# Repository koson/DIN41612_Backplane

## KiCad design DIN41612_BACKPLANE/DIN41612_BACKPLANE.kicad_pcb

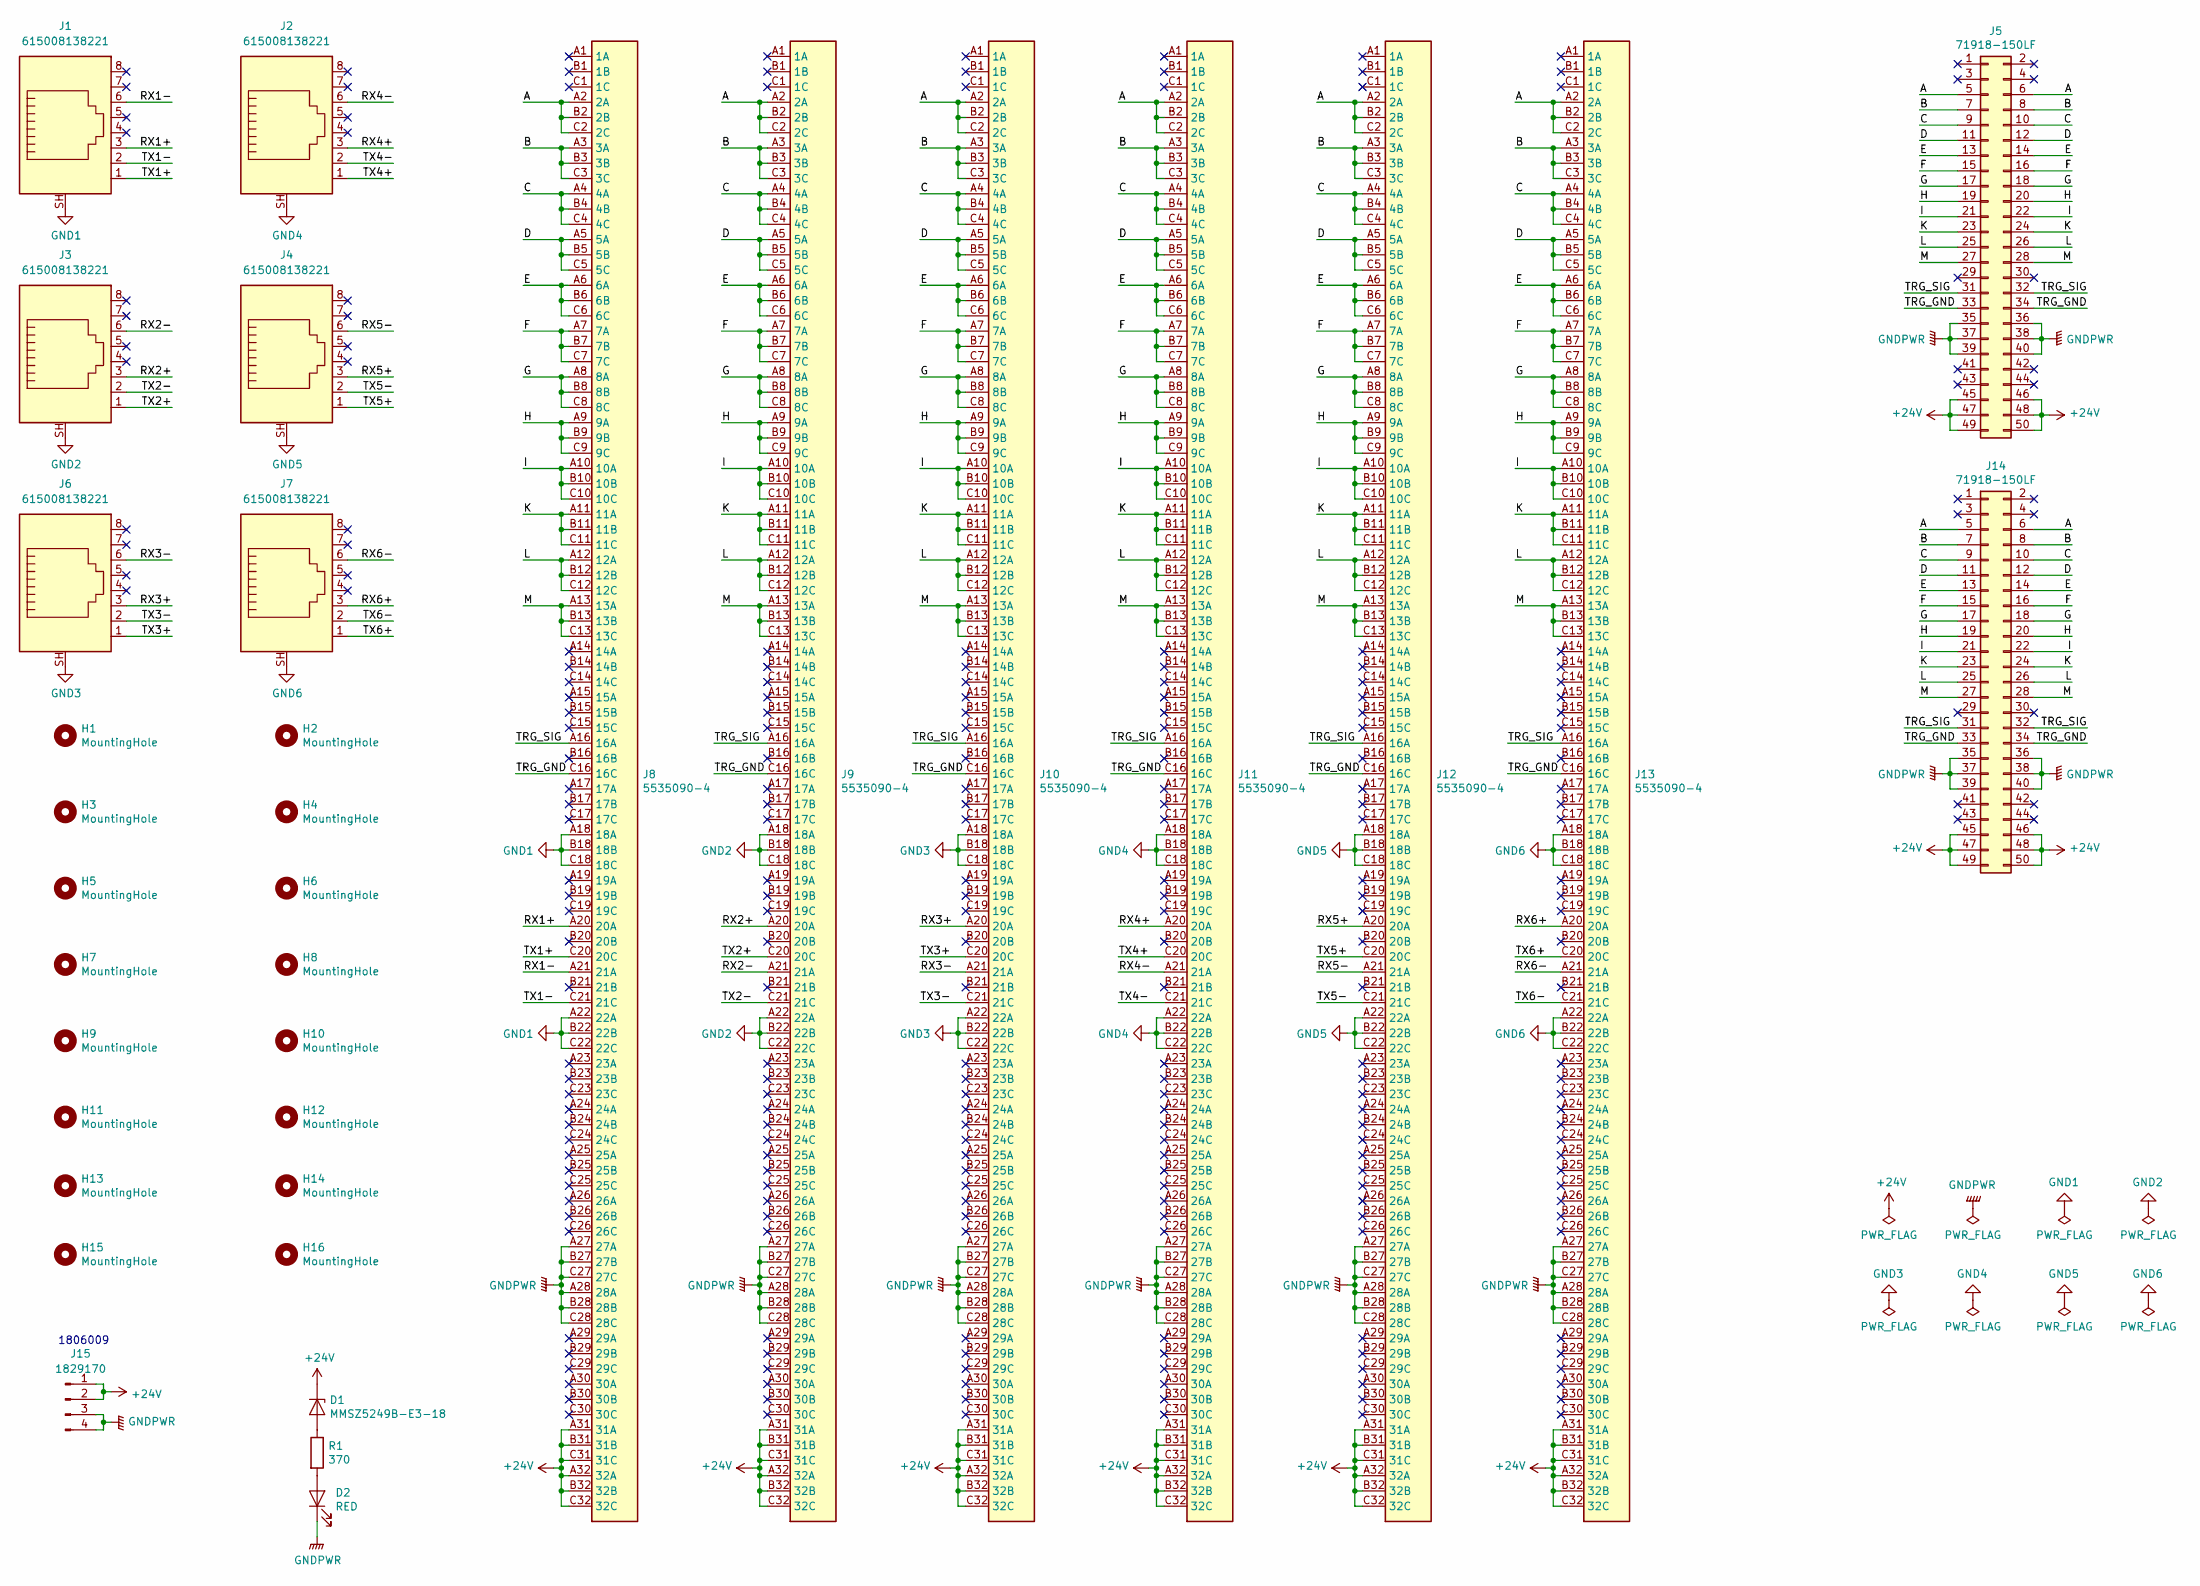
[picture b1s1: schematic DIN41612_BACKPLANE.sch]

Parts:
D1: MMSZ5249B-E3-18; D_SOD-123
D2: RED; LED_0603_1608Metric_Pad1.05x0.95mm_HandSolder
H1, H2, H3, H4, H5, H6, H7, H8, H9, H10, H11, H12, H13, H14, H15, H16: MountingHole; MountingHole_3.2mm_M3_DIN965_Pad
J1, J2, J3, J4, J6, J7: 615008138221
J5, J14: 71918-150LF; IDC-Header_2x25_P2.54mm_Vertical_Lock
J8, J9, J10, J11, J12, J13: 5535090-4; C96ABC
J15: 1829170; PhoenixContact_GMSTBV_2,5_4-GF-7,62_1x04_P7.62mm_Vertical_T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
R1: 370; R_0603_1608Metric_Pad1.05x0.95mm_HandSolder

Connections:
+24V: D1.1 (K), J5.45, J5.46, J5.47, J5.48, J5.49, J5.50, J8.A31 (31A), J8.A32 (32A), J8.B31 (31B), J8.B32 (32B), J8.C31 (31C), J8.C32 (32C), J9.A31 (31A), J9.A32 (32A), J9.B31 (31B), J9.B32 (32B), J9.C31 (31C), J9.C32 (32C), J10.A31 (31A), J10.A32 (32A), J10.B31 (31B), J10.B32 (32B), J10.C31 (31C), J10.C32 (32C), J11.A31 (31A), J11.A32 (32A), J11.B31 (31B), J11.B32 (32B), J11.C31 (31C), J11.C32 (32C), J12.A31 (31A), J12.A32 (32A), J12.B31 (31B), J12.B32 (32B), J12.C31 (31C), J12.C32 (32C), J13.A31 (31A), J13.A32 (32A), J13.B31 (31B), J13.B32 (32B), J13.C31 (31C), J13.C32 (32C), J14.45, J14.46, J14.47, J14.48, J14.49, J14.50, J15.1, J15.2
/A: J5.5, J5.6, J8.A2 (2A), J8.B2 (2B), J8.C2 (2C), J9.A2 (2A), J9.B2 (2B), J9.C2 (2C), J10.A2 (2A), J10.B2 (2B), J10.C2 (2C), J11.A2 (2A), J11.B2 (2B), J11.C2 (2C), J12.A2 (2A), J12.B2 (2B), J12.C2 (2C), J13.A2 (2A), J13.B2 (2B), J13.C2 (2C), J14.5, J14.6
/B: J5.7, J5.8, J8.A3 (3A), J8.B3 (3B), J8.C3 (3C), J9.A3 (3A), J9.B3 (3B), J9.C3 (3C), J10.A3 (3A), J10.B3 (3B), J10.C3 (3C), J11.A3 (3A), J11.B3 (3B), J11.C3 (3C), J12.A3 (3A), J12.B3 (3B), J12.C3 (3C), J13.A3 (3A), J13.B3 (3B), J13.C3 (3C), J14.7, J14.8
/C: J5.9, J5.10, J8.A4 (4A), J8.B4 (4B), J8.C4 (4C), J9.A4 (4A), J9.B4 (4B), J9.C4 (4C), J10.A4 (4A), J10.B4 (4B), J10.C4 (4C), J11.A4 (4A), J11.B4 (4B), J11.C4 (4C), J12.A4 (4A), J12.B4 (4B), J12.C4 (4C), J13.A4 (4A), J13.B4 (4B), J13.C4 (4C), J14.9, J14.10
/D: J5.11, J5.12, J8.A5 (5A), J8.B5 (5B), J8.C5 (5C), J9.A5 (5A), J9.B5 (5B), J9.C5 (5C), J10.A5 (5A), J10.B5 (5B), J10.C5 (5C), J11.A5 (5A), J11.B5 (5B), J11.C5 (5C), J12.A5 (5A), J12.B5 (5B), J12.C5 (5C), J13.A5 (5A), J13.B5 (5B), J13.C5 (5C), J14.11, J14.12
/E: J5.13, J5.14, J8.A6 (6A), J8.B6 (6B), J8.C6 (6C), J9.A6 (6A), J9.B6 (6B), J9.C6 (6C), J10.A6 (6A), J10.B6 (6B), J10.C6 (6C), J11.A6 (6A), J11.B6 (6B), J11.C6 (6C), J12.A6 (6A), J12.B6 (6B), J12.C6 (6C), J13.A6 (6A), J13.B6 (6B), J13.C6 (6C), J14.13, J14.14
/F: J5.15, J5.16, J8.A7 (7A), J8.B7 (7B), J8.C7 (7C), J9.A7 (7A), J9.B7 (7B), J9.C7 (7C), J10.A7 (7A), J10.B7 (7B), J10.C7 (7C), J11.A7 (7A), J11.B7 (7B), J11.C7 (7C), J12.A7 (7A), J12.B7 (7B), J12.C7 (7C), J13.A7 (7A), J13.B7 (7B), J13.C7 (7C), J14.15, J14.16
/G: J5.17, J5.18, J8.A8 (8A), J8.B8 (8B), J8.C8 (8C), J9.A8 (8A), J9.B8 (8B), J9.C8 (8C), J10.A8 (8A), J10.B8 (8B), J10.C8 (8C), J11.A8 (8A), J11.B8 (8B), J11.C8 (8C), J12.A8 (8A), J12.B8 (8B), J12.C8 (8C), J13.A8 (8A), J13.B8 (8B), J13.C8 (8C), J14.17, J14.18
/H: J5.19, J5.20, J8.A9 (9A), J8.B9 (9B), J8.C9 (9C), J9.A9 (9A), J9.B9 (9B), J9.C9 (9C), J10.A9 (9A), J10.B9 (9B), J10.C9 (9C), J11.A9 (9A), J11.B9 (9B), J11.C9 (9C), J12.A9 (9A), J12.B9 (9B), J12.C9 (9C), J13.A9 (9A), J13.B9 (9B), J13.C9 (9C), J14.19, J14.20
/I: J5.21, J5.22, J8.A10 (10A), J8.B10 (10B), J8.C10 (10C), J9.A10 (10A), J9.B10 (10B), J9.C10 (10C), J10.A10 (10A), J10.B10 (10B), J10.C10 (10C), J11.A10 (10A), J11.B10 (10B), J11.C10 (10C), J12.A10 (10A), J12.B10 (10B), J12.C10 (10C), J13.A10 (10A), J13.B10 (10B), J13.C10 (10C), J14.21, J14.22
/K: J5.23, J5.24, J8.A11 (11A), J8.B11 (11B), J8.C11 (11C), J9.A11 (11A), J9.B11 (11B), J9.C11 (11C), J10.A11 (11A), J10.B11 (11B), J10.C11 (11C), J11.A11 (11A), J11.B11 (11B), J11.C11 (11C), J12.A11 (11A), J12.B11 (11B), J12.C11 (11C), J13.A11 (11A), J13.B11 (11B), J13.C11 (11C), J14.23, J14.24
/L: J5.25, J5.26, J8.A12 (12A), J8.B12 (12B), J8.C12 (12C), J9.A12 (12A), J9.B12 (12B), J9.C12 (12C), J10.A12 (12A), J10.B12 (12B), J10.C12 (12C), J11.A12 (12A), J11.B12 (12B), J11.C12 (12C), J12.A12 (12A), J12.B12 (12B), J12.C12 (12C), J13.A12 (12A), J13.B12 (12B), J13.C12 (12C), J14.25, J14.26
/M: J5.27, J5.28, J8.A13 (13A), J8.B13 (13B), J8.C13 (13C), J9.A13 (13A), J9.B13 (13B), J9.C13 (13C), J10.A13 (13A), J10.B13 (13B), J10.C13 (13C), J11.A13 (13A), J11.B13 (13B), J11.C13 (13C), J12.A13 (13A), J12.B13 (13B), J12.C13 (13C), J13.A13 (13A), J13.B13 (13B), J13.C13 (13C), J14.27, J14.28
/RX1+: J1.3, J8.A20 (20A)
/RX1-: J1.6, J8.A21 (21A)
/RX2+: J3.3, J9.A20 (20A)
/RX2-: J3.6, J9.A21 (21A)
/RX3+: J6.3, J10.A20 (20A)
/RX3-: J6.6, J10.A21 (21A)
/RX4+: J2.3, J11.A20 (20A)
/RX4-: J2.6, J11.A21 (21A)
/RX5+: J4.3, J12.A20 (20A)
/RX5-: J4.6, J12.A21 (21A)
/RX6+: J7.3, J13.A20 (20A)
/RX6-: J7.6, J13.A21 (21A)
/TRG_GND: J5.33, J5.34, J8.C16 (16C), J9.C16 (16C), J10.C16 (16C), J11.C16 (16C), J12.C16 (16C), J13.C16 (16C), J14.33, J14.34
/TRG_SIG: J5.31, J5.32, J8.A16 (16A), J9.A16 (16A), J10.A16 (16A), J11.A16 (16A), J12.A16 (16A), J13.A16 (16A), J14.31, J14.32
/TX1+: J1.1, J8.C20 (20C)
/TX1-: J1.2, J8.C21 (21C)
/TX2+: J3.1, J9.C20 (20C)
/TX2-: J3.2, J9.C21 (21C)
/TX3+: J6.1, J10.C20 (20C)
/TX3-: J6.2, J10.C21 (21C)
/TX4+: J2.1, J11.C20 (20C)
/TX4-: J2.2, J11.C21 (21C)
/TX5+: J4.1, J12.C20 (20C)
/TX5-: J4.2, J12.C21 (21C)
/TX6+: J7.1, J13.C20 (20C)
/TX6-: J7.2, J13.C21 (21C)
GND1: J1.SH, J8.A18 (18A), J8.A22 (22A), J8.B18 (18B), J8.B22 (22B), J8.C18 (18C), J8.C22 (22C)
GND2: J3.SH, J9.A18 (18A), J9.A22 (22A), J9.B18 (18B), J9.B22 (22B), J9.C18 (18C), J9.C22 (22C)
GND3: J6.SH, J10.A18 (18A), J10.A22 (22A), J10.B18 (18B), J10.B22 (22B), J10.C18 (18C), J10.C22 (22C)
GND4: J2.SH, J11.A18 (18A), J11.A22 (22A), J11.B18 (18B), J11.B22 (22B), J11.C18 (18C), J11.C22 (22C)
GND5: J4.SH, J12.A18 (18A), J12.A22 (22A), J12.B18 (18B), J12.B22 (22B), J12.C18 (18C), J12.C22 (22C)
GND6: J7.SH, J13.A18 (18A), J13.A22 (22A), J13.B18 (18B), J13.B22 (22B), J13.C18 (18C), J13.C22 (22C)
GNDPWR: D2.1 (K), J5.35, J5.36, J5.37, J5.38, J5.39, J5.40, J8.A27 (27A), J8.A28 (28A), J8.B27 (27B), J8.B28 (28B), J8.C27 (27C), J8.C28 (28C), J9.A27 (27A), J9.A28 (28A), J9.B27 (27B), J9.B28 (28B), J9.C27 (27C), J9.C28 (28C), J10.A27 (27A), J10.A28 (28A), J10.B27 (27B), J10.B28 (28B), J10.C27 (27C), J10.C28 (28C), J11.A27 (27A), J11.A28 (28A), J11.B27 (27B), J11.B28 (28B), J11.C27 (27C), J11.C28 (28C), J12.A27 (27A), J12.A28 (28A), J12.B27 (27B), J12.B28 (28B), J12.C27 (27C), J12.C28 (28C), J13.A27 (27A), J13.A28 (28A), J13.B27 (27B), J13.B28 (28B), J13.C27 (27C), J13.C28 (28C), J14.35, J14.36, J14.37, J14.38, J14.39, J14.40, J15.3, J15.4
unnamed: D1.2 (A), R1.1
unnamed: D2.2 (A), R1.2

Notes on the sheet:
1806009

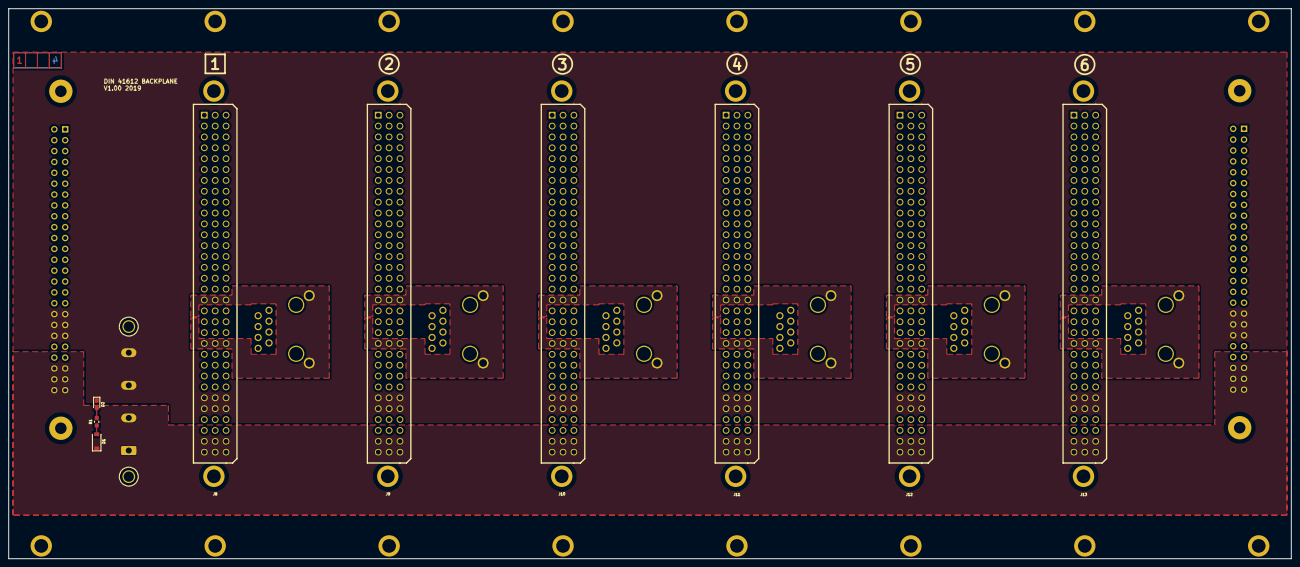
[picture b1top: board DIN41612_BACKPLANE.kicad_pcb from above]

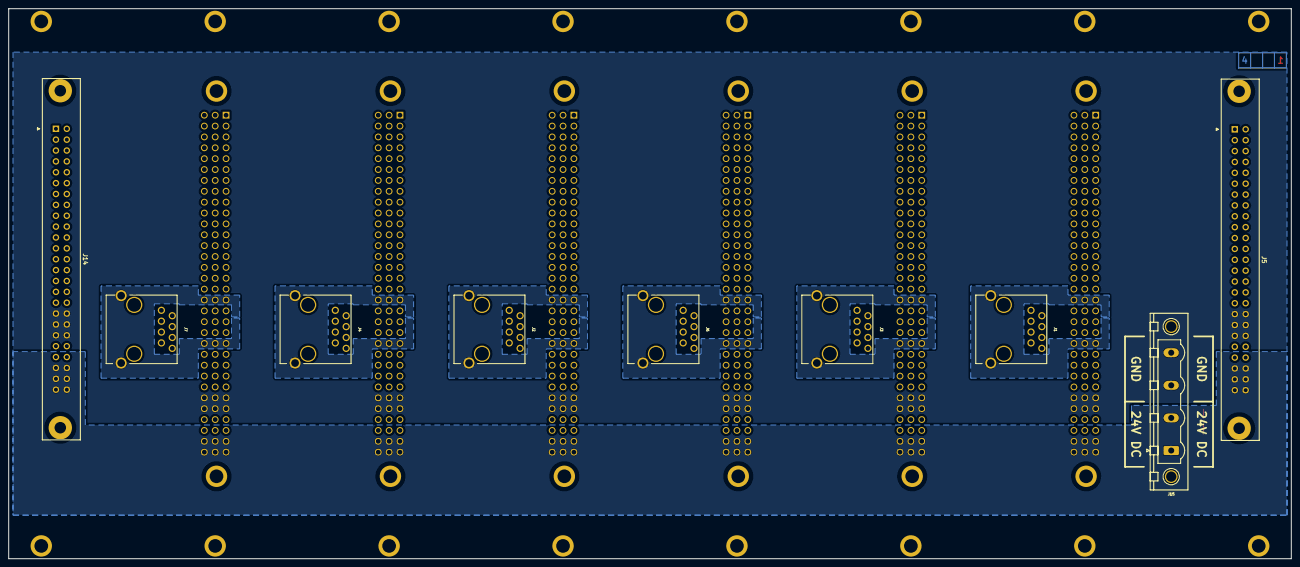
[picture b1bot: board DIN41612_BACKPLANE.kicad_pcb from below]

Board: 4 copper layers, 299.7 x 128.5 mm, 34 parts (9 on the bottom side), 48 nets.

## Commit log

2019-11-07 Schematic development.
2019-11-09 Schematic and PCB done.
2019-11-10 Added trigger signal.
2019-11-14 Fixed bug in PCB.
2024-04-09 kicad
